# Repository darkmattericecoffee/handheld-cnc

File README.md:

## Description
Compass is a DIY handheld CNC router designed to make CNC machining more accessible.

Unlike traditional CNC machines that move a cutting tool within a fixed workspace, Compass relies on users to guide the device around the workpiece directly. It automatically adjusts the cutting tool to stay on the programmed design path, enabling a significantly smaller device footprint while still handling large-scale cuts.

This is all accomplished using optical flow mouse sensors to track the position of the device, as well as a lead screw driven gantry to adjust the tool. The brains are a Teensy 4.1 microcontroller.

## Getting Started
This repo contains all of the source to build a Handheld CNC Router: the firmware, CAD files for 3D printing/manufacturing, BOM, and cable diagrams.

### Navigation
Internal
- [main](main/) - main firmware (written for [PlatformIO](https://docs.platformio.org/en/latest/core/quickstart.html) usage)
- [cad](cad/) - custom hardware (3D prints, laser cut sheet metal, cable harnesses)
- [pcb](pcb/) - printed circuit board designs for motherboard and sensors
- [dev](dev/) - development folder for debugging and testing

External
- [BOM](https://docs.google.com/spreadsheets/d/12QS1CGSAB-lqKIOotCXDaXmJv9cjfRvVEAgQbRd7MnY/edit?usp=sharing)
- [Assembly Instructions](https://drive.google.com/drive/folders/1fIALrTWUbJRqTl93RGrUaR8dMfO7AI_g?usp=sharing)

## Disclaimer
This project is a work-in-progress. Development is rapidly occurring, so design files and firmware may change.

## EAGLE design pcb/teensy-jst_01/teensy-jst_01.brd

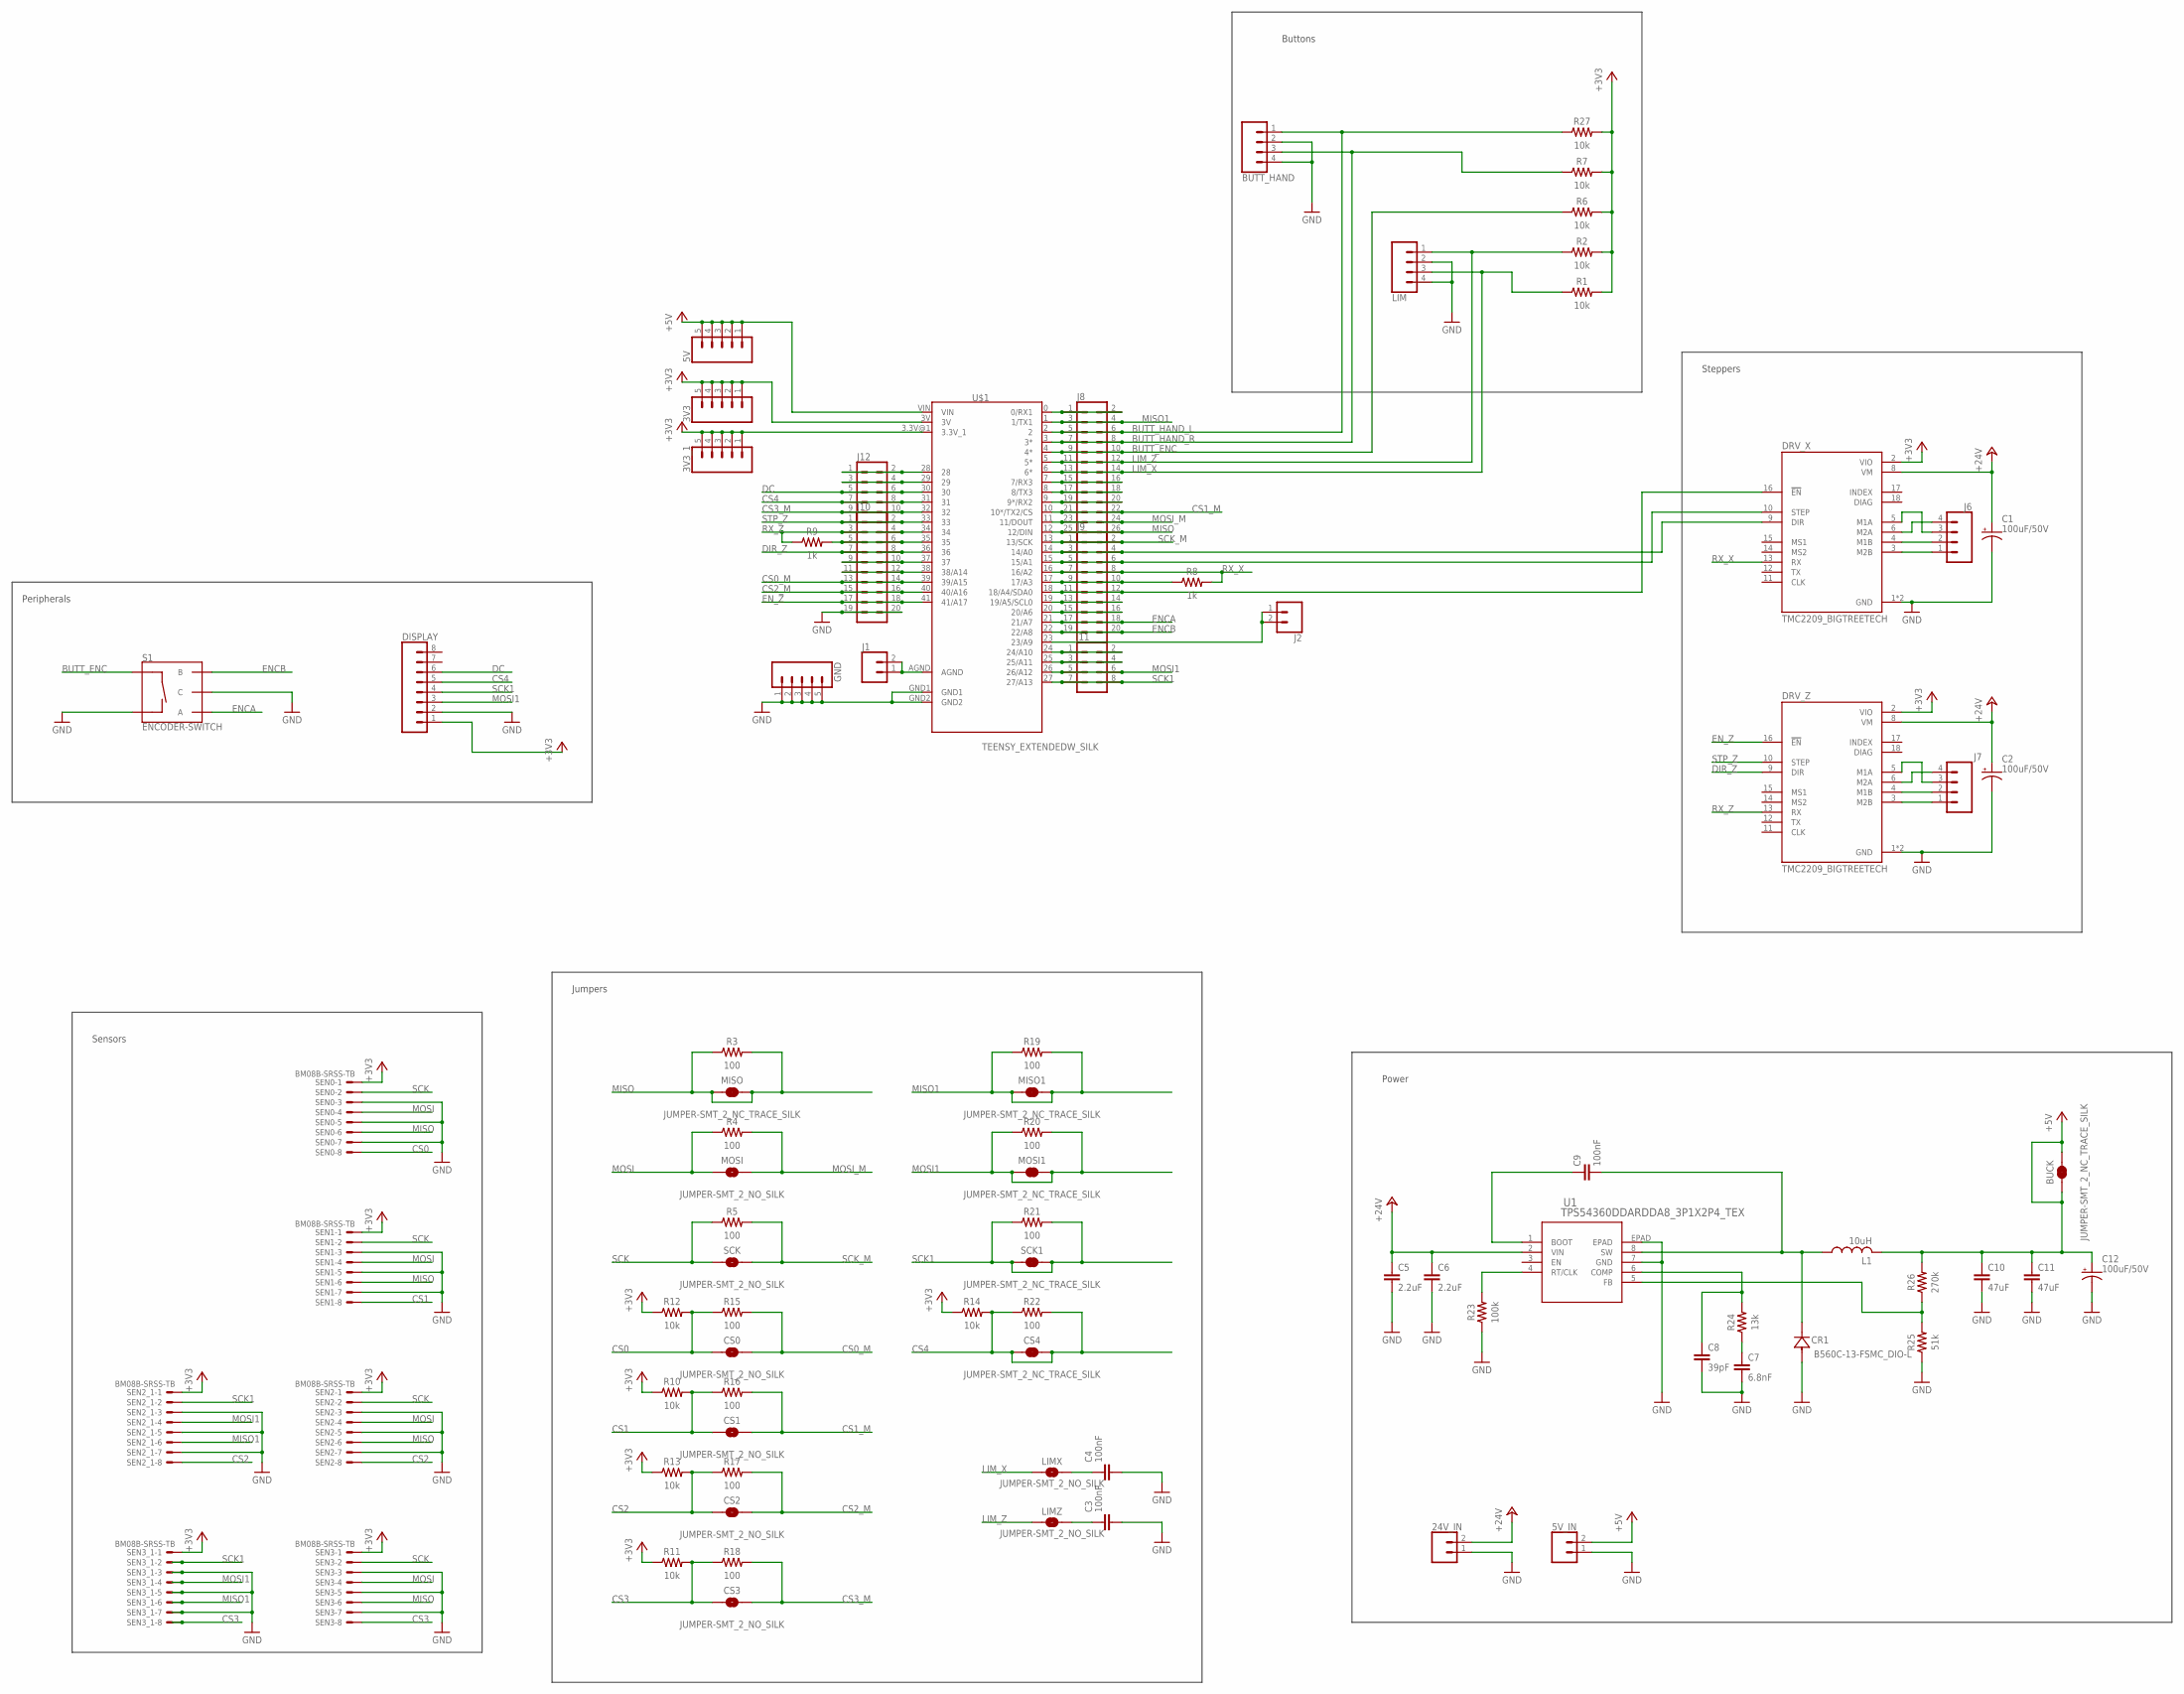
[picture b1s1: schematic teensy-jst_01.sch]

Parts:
3V3, 3V3_1, 5V: CONN_05PTH; 1X05
5V_IN, 24V_IN: CONN_025MM; SCREWTERMINAL-5MM-2
BUCK: JUMPER-SMT_2_NC_TRACE_SILK; SMT-JUMPER_2_NC_TRACE_SILK
BUTT_HAND: CONN_041X04_NO_SILK; 1X04_NO_SILK
C1, C2, C12: 100uF/50V; E5-6
C3, C4: 100nF; C0603
C5, C6: 2.2uF; C0603
C7: 6.8nF; C0402
C8: 39pF; C0402
C9: 100nF; C0402
C10, C11: 47uF; C0603
CR1: B560C-13-FSMC_DIO-L; SMC_DIO-L
CS0, CS1, CS2, CS3: JUMPER-SMT_2_NO_SILK; SMT-JUMPER_2_NO_SILK
CS4: JUMPER-SMT_2_NC_TRACE_SILK; SMT-JUMPER_2_NC_TRACE_SILK
DISPLAY: CONN_08"; 1X08
DRV_X: TMC2209_BIGTREETECH; MODULE_TMC2209_BIGTREETECH
DRV_Z: TMC2209_BIGTREETECH; MODULE_TMC2209_BIGTREETECH
GND: CONN_05PTH; 1X05
J1, J2: CONN_02; 1X02
J6, J7: CONN_04PTH; 1X04
J8: CONN_13X22X13; 2X13
J9, J10: CONN_10X2; 2X10
J11: CONN_04X2; 2X4
J12: CONN_05X2PTH; 2X5
L1: 10uH; MWSA0503S-100MT
LIM: CONN_041X04_NO_SILK; 1X04_NO_SILK
LIMX: JUMPER-SMT_2_NO_SILK; SMT-JUMPER_2_NO_SILK
LIMZ: JUMPER-SMT_2_NO_SILK; SMT-JUMPER_2_NO_SILK
MISO, MISO1: JUMPER-SMT_2_NC_TRACE_SILK; SMT-JUMPER_2_NC_TRACE_SILK
MOSI: JUMPER-SMT_2_NO_SILK; SMT-JUMPER_2_NO_SILK
MOSI1: JUMPER-SMT_2_NC_TRACE_SILK; SMT-JUMPER_2_NC_TRACE_SILK
R1, R2, R6, R7, R10, R11, R12, R13, R14, R27: 10k; RESC1608X60
R3, R4, R5, R15, R16, R17, R18, R19, R20, R21, R22: 100; RESC1608X60
R8, R9: 1k; RESC1608X60
R23: 100k; RESC1005X40
R24: 13k; RESC1005X40
R25: 51k; RESC1005X40
R26: 270k; RESC1005X40
S1: ENCODER-SWITCH; ROTARY_ENC_PLAIN
SCK: JUMPER-SMT_2_NO_SILK; SMT-JUMPER_2_NO_SILK
SCK1: JUMPER-SMT_2_NC_TRACE_SILK; SMT-JUMPER_2_NC_TRACE_SILK
SEN0, SEN1, SEN2, SEN2_1, SEN3, SEN3_1: BM08B-SRSS-TB
U1: TPS54360DDARDDA8_3P1X2P4_TEX; DDA8_3P1X2P4_TEX
U$1: TEENSY_EXTENDEDW_SILK; TEENSY_EXTENDED

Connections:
+3V3: 3V3.1, 3V3.2, 3V3.3, 3V3.4, 3V3.5, 3V3_1.1, 3V3_1.2, 3V3_1.3, 3V3_1.4, 3V3_1.5, DISPLAY.1, DRV_X.2 (VIO), DRV_Z.2 (VIO), R1.2, R2.2, R6.2, R7.2, R10.1, R11.1, R12.1, R13.1, R14.1, R27.2, SEN0.1, SEN1.1, SEN2.1, SEN2_1.1, SEN3.1, SEN3_1.1, U$1.3.3V@1 (3.3V_1), U$1.3V
+5V: 5V.1, 5V.2, 5V.3, 5V.4, 5V.5, 5V_IN.2, BUCK.1, BUCK.2, C10.1, C11.1, C12.+, L1.2, R26.2, U$1.VIN
+24V: 24V_IN.2, C1.+, C2.+, C5.1, C6.1, DRV_X.8 (VM), DRV_Z.8 (VM), U1.2 (VIN)
BUTT_ENC: J8.9, J8.10, R6.1, S1.SW+, U$1.4 (4*)
BUTT_HAND_L: BUTT_HAND.1, J8.5, J8.6, R27.1, U$1.2
BUTT_HAND_R: BUTT_HAND.3, J8.7, J8.8, R7.1, U$1.3 (3*)
CS0: CS0.1, R12.2, R15.1, SEN0.8
CS0_M: CS0.2, J10.13, J10.14, R15.2, U$1.39 (39/A15)
CS1: CS1.1, R10.2, R16.1, SEN1.8
CS1_M: CS1.2, J8.21, J8.22, R16.2, U$1.10 (10*/TX2/CS)
CS2: CS2.1, R13.2, R17.1, SEN2.8, SEN2_1.8
CS2_M: CS2.2, J10.15, J10.16, R17.2, U$1.40 (40/A16)
CS3: CS3.1, R11.2, R18.1, SEN3.8, SEN3_1.8
CS3_M: CS3.2, J12.9, J12.10, R18.2, U$1.32
CS4: CS4.1, CS4.2, DISPLAY.5, J12.7, J12.8, R14.2, R22.1, R22.2, U$1.31
DC: DISPLAY.6, J12.5, J12.6, U$1.30
DIR_Z: DRV_Z.9 (DIR), J10.7, J10.8, U$1.36
ENCA: J9.17, J9.18, S1.A, U$1.21 (21/A7)
ENCB: J9.19, J9.20, S1.B, U$1.22 (22/A8)
EN_Z: DRV_Z.16 (!EN), J10.17, J10.18, U$1.41 (41/A17)
GND: 5V_IN.1, 24V_IN.1, BUTT_HAND.2, BUTT_HAND.4, C1.-, C2.-, C3.2, C4.2, C5.2, C6.2, C7.2, C8.2, C10.2, C11.2, C12.-, CR1.2, DISPLAY.2, DRV_X.1 (GND), DRV_X.7 (GND), DRV_Z.1 (GND), DRV_Z.7 (GND), GND.1, GND.2, GND.3, GND.4, GND.5, J10.19, J10.20, LIM.2, LIM.4, R23.1, R25.1, S1.C, S1.SW-, SEN0.3, SEN0.5, SEN0.7, SEN1.3, SEN1.5, SEN1.7, SEN2.3, SEN2.5, SEN2.7, SEN2_1.3, SEN2_1.5, SEN2_1.7, SEN3.3, SEN3.5, SEN3.7, SEN3_1.3, SEN3_1.5, SEN3_1.7, U1.7 (GND), U1.EPAD, U$1.GND1, U$1.GND2
LIM_X: J8.13, J8.14, LIM.3, LIMX.1, R1.1, U$1.6 (6*)
LIM_Z: J8.11, J8.12, LIM.1, LIMZ.1, R2.1, U$1.5 (5*)
MISO: J8.25, J8.26, MISO.1, MISO.2, R3.1, R3.2, SEN0.6, SEN1.6, SEN2.6, SEN3.6, U$1.12 (12/DIN)
MISO1: J8.3, J8.4, MISO1.1, MISO1.2, R19.1, R19.2, SEN2_1.6, SEN3_1.6, U$1.1 (1/TX1)
MOSI: MOSI.1, R4.1, SEN0.4, SEN1.4, SEN2.4, SEN3.4
MOSI1: DISPLAY.3, J11.5, J11.6, MOSI1.1, MOSI1.2, R20.1, R20.2, SEN2_1.4, SEN3_1.4, U$1.26 (26/A12)
MOSI_M: J8.23, J8.24, MOSI.2, R4.2, U$1.11 (11/DOUT)
MS1_Z: J10.9, J10.10, U$1.37
MS2_Z: J10.11, J10.12, U$1.38 (38/A14)
unnamed: J12.1, J12.2, U$1.28
unnamed: J11.1, J11.2, U$1.24 (24/A10)
unnamed: J1.1, J1.2, U$1.AGND
unnamed: J2.1, J2.2, U$1.23 (23/A9)
unnamed: J12.3, J12.4, U$1.29
unnamed: R23.2, U1.4 (RT/CLK)
unnamed: J8.15, J8.16, U$1.7 (7/RX3)
unnamed: C7.1, R24.1
unnamed: DRV_X.9 (DIR), J9.3, J9.4, U$1.14 (14/A0)
unnamed: DRV_Z.6 (M2A), J7.4
unnamed: DRV_X.10 (STEP), J9.5, J9.6, U$1.15 (15/A1)
unnamed: C8.1, R24.2, U1.6 (COMP)
unnamed: DRV_Z.5 (M1A), J7.3
unnamed: J9.13, J9.14, U$1.19 (19/A5/SCL0)
unnamed: DRV_X.6 (M2A), J6.4
unnamed: DRV_X.5 (M1A), J6.3
unnamed: R25.2, R26.1, U1.5 (FB)
unnamed: DRV_Z.4 (M1B), J7.2
unnamed: DRV_Z.3 (M2B), J7.1
unnamed: J11.3, J11.4, U$1.25 (25/A11)
unnamed: C3.1, LIMZ.2
unnamed: DRV_X.4 (M1B), J6.2
unnamed: DRV_X.3 (M2B), J6.1
unnamed: J9.15, J9.16, U$1.20 (20/A6)
unnamed: DRV_X.16 (!EN), J9.11, J9.12, U$1.18 (18/A4/SDA0)
unnamed: J9.9, J9.10, R8.1, U$1.17 (17/A3)
unnamed: C9.2, CR1.1, L1.1, U1.8 (SW)
unnamed: C4.1, LIMX.2
unnamed: C9.1, U1.1 (BOOT)
unnamed: J8.17, J8.18, U$1.8 (8/TX3)
unnamed: J8.1, J8.2, U$1.0 (0/RX1)
unnamed: J8.19, J8.20, U$1.9 (9*/RX2)
unnamed: J10.5, J10.6, R9.2, U$1.35
RX_X: DRV_X.13 (RX), J9.7, J9.8, R8.2, U$1.16 (16/A2)
RX_Z: DRV_Z.13 (RX), J10.3, J10.4, R9.1, U$1.34
SCK: R5.1, SCK.1, SEN0.2, SEN1.2, SEN2.2, SEN3.2
SCK1: DISPLAY.4, J11.7, J11.8, R21.1, R21.2, SCK1.1, SCK1.2, SEN2_1.2, SEN3_1.2, U$1.27 (27/A13)
SCK_M: J9.1, J9.2, R5.2, SCK.2, U$1.13 (13/SCK)
STP_Z: DRV_Z.10 (STEP), J10.1, J10.2, U$1.33

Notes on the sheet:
Jumpers
Peripherals
Steppers
Sensors
Power
Buttons

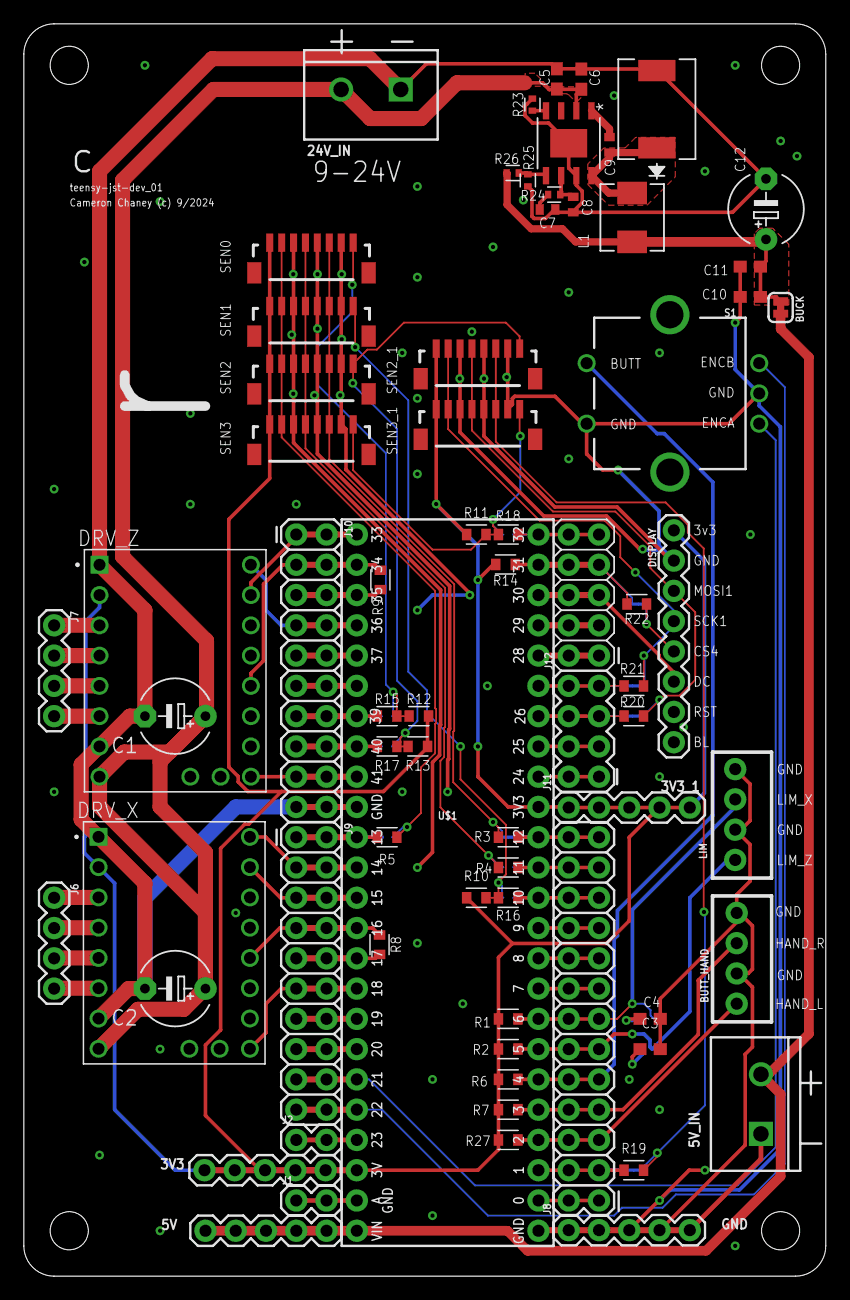
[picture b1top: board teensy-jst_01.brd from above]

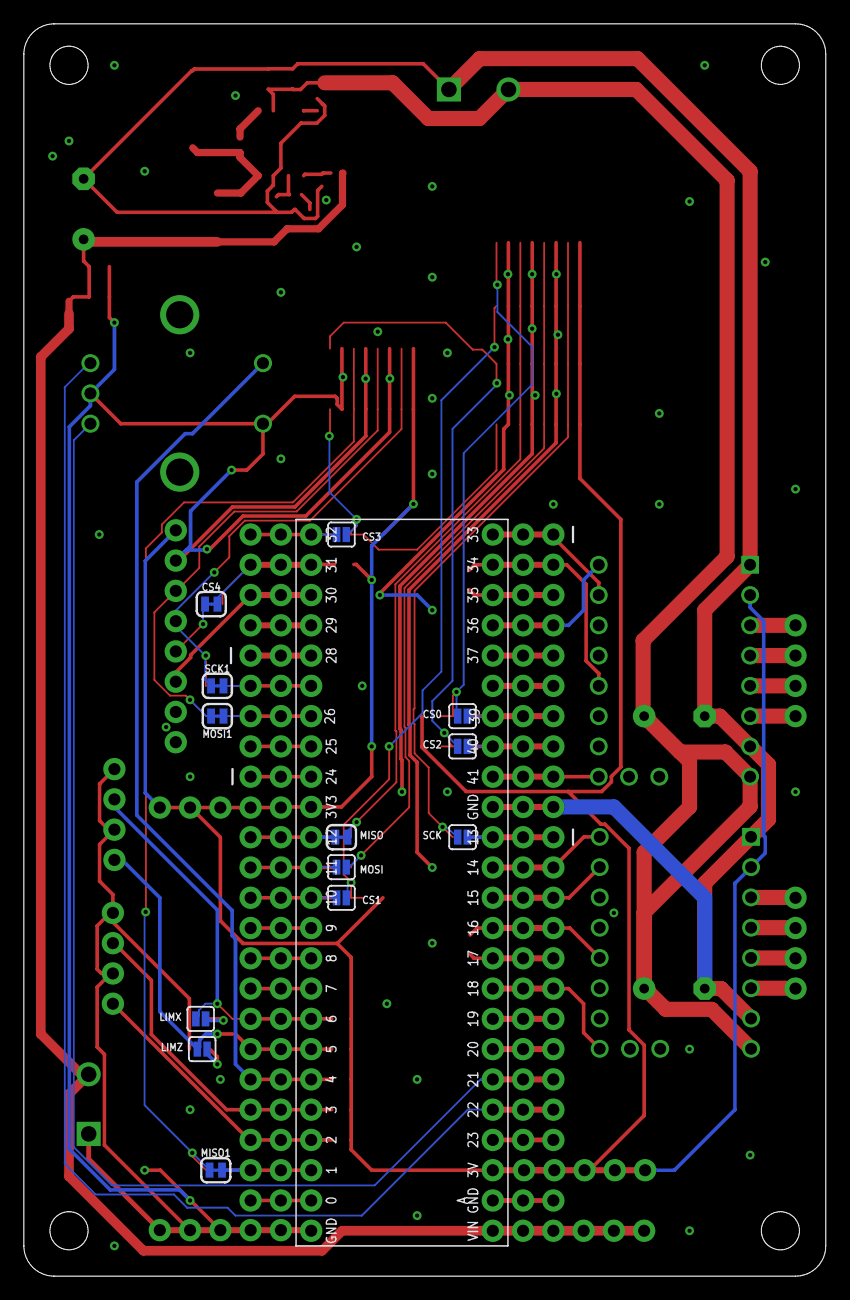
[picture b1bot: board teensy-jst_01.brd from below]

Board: 2 copper layers, 67.3 x 105.1 mm, 84 parts (13 on the bottom side), 69 nets.

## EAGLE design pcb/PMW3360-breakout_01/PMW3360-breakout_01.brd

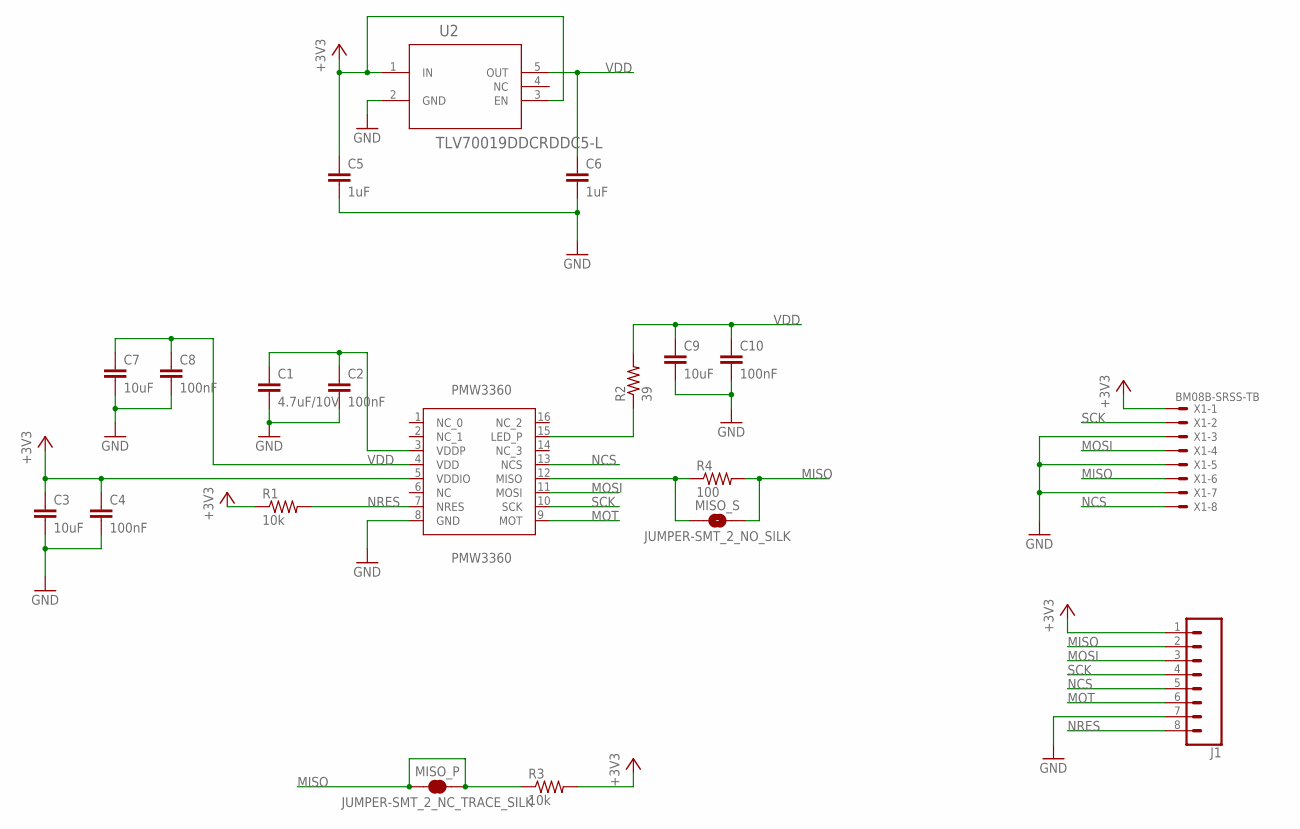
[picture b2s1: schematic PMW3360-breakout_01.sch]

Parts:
C1: 4.7uF/10V; C0603
C2, C4, C8, C10: 100nF; C0402
C3, C7, C9: 10uF; C0402
C5, C6: 1uF; C0402
J1: CONN_08"; 1X08
MISO_P: JUMPER-SMT_2_NC_TRACE_SILK; SMT-JUMPER_2_NC_TRACE_SILK
MISO_S: JUMPER-SMT_2_NO_SILK; SMT-JUMPER_2_NO_SILK
PMW3360: PMW3360
R1, R3: 10k; R0402
R2: 39; R0402
R4: 100; R0402
U2: TLV70019DDCRDDC5-L; DDC5-L
X1: BM08B-SRSS-TB

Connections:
+3V3: C3.1, C4.1, C5.1, J1.1, PMW3360.5 (VDDIO), R1.1, R3.2, U2.1 (IN), U2.3 (EN), X1.1
GND: C1.2, C2.2, C3.2, C4.2, C5.2, C6.2, C7.2, C8.2, C9.2, C10.2, J1.7, PMW3360.8 (GND), U2.2 (GND), X1.3, X1.5, X1.7
MISO: J1.2, MISO_P.1, MISO_P.2, MISO_S.2, R3.1, R4.2, X1.6
MOSI: J1.3, PMW3360.11 (MOSI), X1.4
MOT: J1.6, PMW3360.9 (MOT)
unnamed: PMW3360.15 (LED_P), R2.1
unnamed: C1.1, C2.1, PMW3360.3 (VDDP)
unnamed: MISO_S.1, PMW3360.12 (MISO), R4.1
NCS: J1.5, PMW3360.13 (NCS), X1.8
NRES: J1.8, PMW3360.7 (NRES), R1.2
SCK: J1.4, PMW3360.10 (SCK), X1.2
VDD: C6.1, C7.1, C8.1, C9.1, C10.1, PMW3360.4 (VDD), R2.2, U2.5 (OUT)

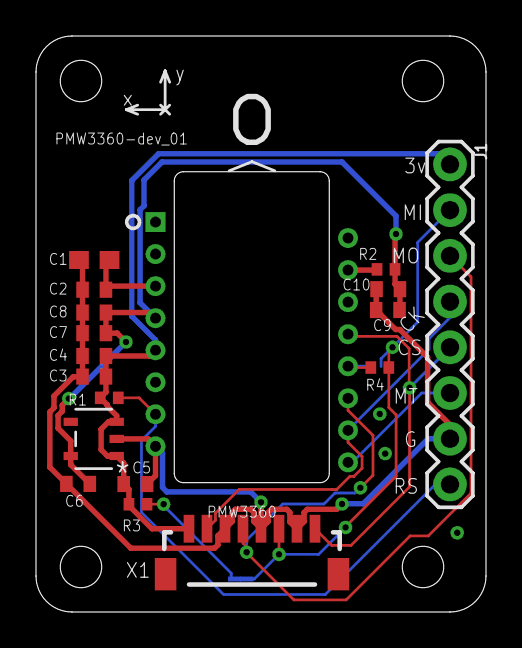
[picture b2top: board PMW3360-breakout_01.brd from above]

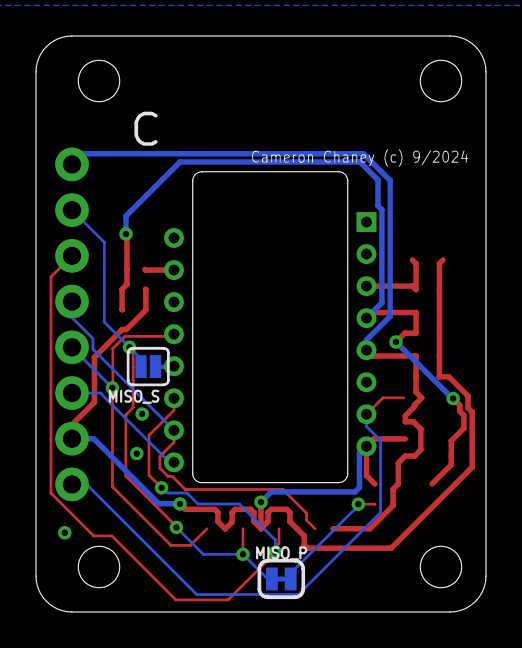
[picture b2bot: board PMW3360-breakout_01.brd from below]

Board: 2 copper layers, 25.0 x 32.0 mm, 20 parts (2 on the bottom side), 12 nets.

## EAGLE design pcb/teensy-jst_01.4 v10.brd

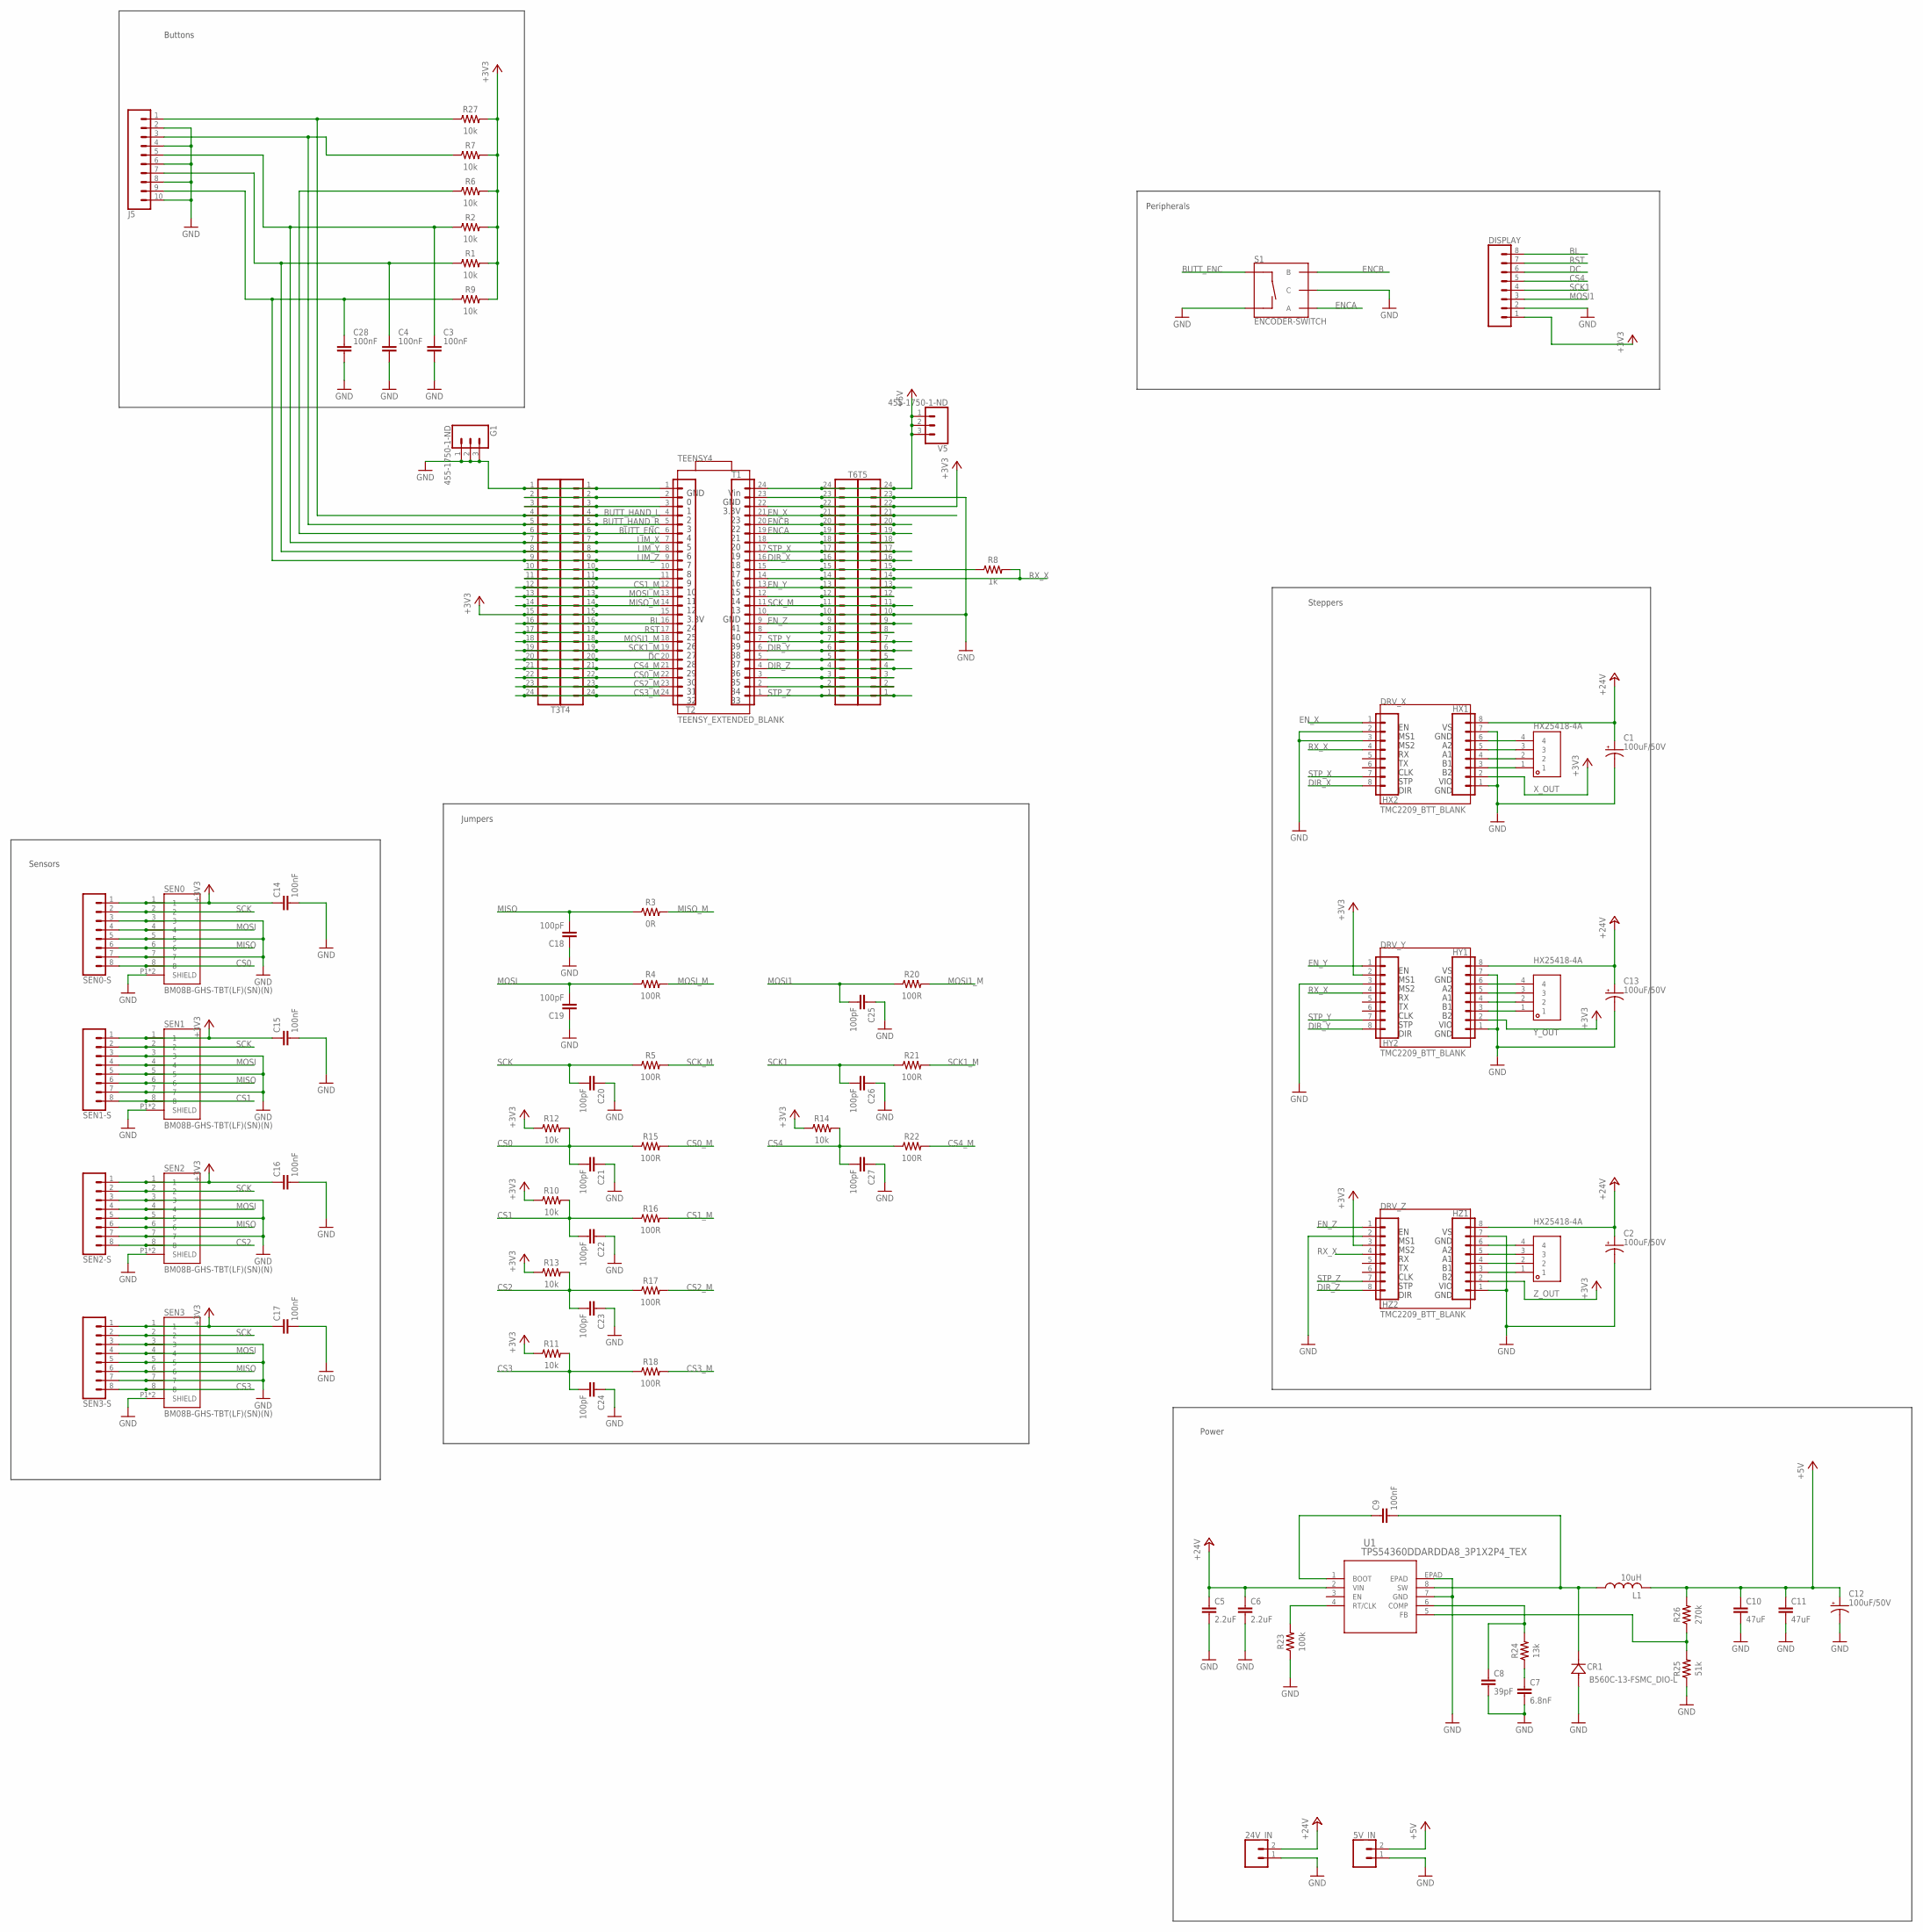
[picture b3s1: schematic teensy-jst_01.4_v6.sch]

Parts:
5V_IN, 24V_IN: CONN_025MM; SCREWTERMINAL-5MM-2
C1, C2, C12, C13: 100uF/50V; PANASONIC_D
C3, C4, C28: 100nF; CAPC1608X85
C5, C6: 2.2uF; CAPC1608X85
C7: 6.8nF; CAPC1608X85
C8: 39pF; CAPC1005X60
C9, C14, C15, C16, C17: 100nF; CAPC1005X60
C10, C11: 47uF; CAPC2012X110
C18, C19, C20, C21, C22, C23, C24, C25, C26, C27: 100pF; CAPC1005X60
CR1: B560C-13-FSMC_DIO-L; SMC_DIO-L
DISPLAY: CONN_08"; 1X08
DRV_X: TMC2209_BTT_BLANK; MODULE_TMC2209_BTT_BLANK
DRV_Y: TMC2209_BTT_BLANK; MODULE_TMC2209_BTT_BLANK
DRV_Z: TMC2209_BTT_BLANK; MODULE_TMC2209_BTT_BLANK
G1: 455-1750-1-ND; 1X03
HX1, HX2: CONN_08"; 1X08
HY1, HY2: CONN_08"; 1X08
HZ1, HZ2: CONN_08"; 1X08
J5: CONN_10"; 1X10
L1: 10uH; MWSA0503S-100MT
R1, R2, R6, R7, R9, R10, R11, R12, R13, R14, R27: 10k; RESC1608X60
R3: 0R; RESC1608X60
R4, R5, R15, R16, R17, R18, R20, R21, R22: 100R; RESC1608X60
R8: 1k; RESC1608X60
R23: 100k; RESC1005X40
R24: 13k; RESC1608X60
R25: 51k; RESC1608X60
R26: 270k; RESC1005X40
S1: ENCODER-SWITCH; ROTARY_ENC_PLAIN
SEN0, SEN1, SEN2, SEN3: BM08B-GHS-TBT(LF)(SN)(N); JST_BM08B-GHS-TBT(LF)(SN)(N)
SEN0-S, SEN1-S, SEN2-S, SEN3-S: CONN_08"; 1X08
T1, T2, T3, T4, T5, T6: CONN_24; 1X24
TEENSY4: TEENSY_EXTENDED_BLANK
U1: TPS54360DDARDDA8_3P1X2P4_TEX; DDA8_3P1X2P4_TEX
V5: 455-1750-1-ND; 1X03
X_OUT: HX25418-4A
Y_OUT: HX25418-4A
Z_OUT: HX25418-4A

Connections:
+3V3: C14.1, C15.1, C16.1, C17.1, DISPLAY.1, HX1.2, HY1.2, HY2.2, HZ1.2, HZ2.3, R1.2, R2.2, R6.2, R7.2, R9.2, R10.1, R11.1, R12.1, R13.1, R14.1, R27.2, SEN0.1, SEN0-S.1, SEN1.1, SEN1-S.1, SEN2.1, SEN2-S.1, SEN3.1, SEN3-S.1, T1.22, T2.15, T3.15, T4.15, T5.22, T6.22
+5V: 5V_IN.2, C10.1, C11.1, C12.+, L1.2, R26.2, T1.24, T5.24, T6.24, V5.1, V5.2, V5.3
+24V: 24V_IN.2, C1.+, C2.+, C5.1, C6.1, C13.+, HX1.8, HY1.8, HZ1.8, U1.2 (VIN)
BL: DISPLAY.8, T2.16, T3.16, T4.16
BUTT_ENC: R6.1, S1.SW+, T2.6, T3.6, T4.6
BUTT_HAND_L: J5.1, R27.1, T2.4, T3.4, T4.4
BUTT_HAND_R: J5.3, R7.1, T2.5, T3.5, T4.5
CS0: C21.2, R12.2, R15.1, SEN0.8, SEN0-S.8
CS0_M: R15.2, T2.22, T3.22, T4.22
CS1: C22.2, R10.2, R16.1, SEN1.8, SEN1-S.8
CS1_M: R16.2, T2.12, T3.12, T4.12
CS2: C23.2, R13.2, R17.1, SEN2.8, SEN2-S.8
CS2_M: R17.2, T2.23, T3.23, T4.23
CS3: C24.2, R11.2, R18.1, SEN3.8, SEN3-S.8
CS3_M: R18.2, T2.24, T3.24, T4.24
CS4: C27.2, DISPLAY.5, R14.2, R22.1
CS4_M: R22.2, T2.21, T3.21, T4.21
DC: DISPLAY.6, T2.20, T3.20, T4.20
DIR_X: HX2.8, T1.16, T5.16, T6.16
DIR_Y: HY2.8, T1.6, T5.6, T6.6
DIR_Z: HZ2.8, T1.4, T5.4, T6.4
ENCA: S1.A, T1.19, T5.19, T6.19
ENCB: S1.B, T1.20, T5.20, T6.20
EN_X: HX2.1, T1.21, T5.21, T6.21
EN_Y: HY2.1, T1.13, T5.13, T6.13
EN_Z: HZ2.1, T1.9, T5.9, T6.9
GND: 5V_IN.1, 24V_IN.1, C1.-, C2.-, C3.2, C4.2, C5.2, C6.2, C7.2, C8.2, C10.2, C11.2, C12.-, C13.-, C14.2, C15.2, C16.2, C17.2, C18.1, C19.1, C20.1, C21.1, C22.1, C23.1, C24.1, C25.1, C26.1, C27.1, C28.2, CR1.2, DISPLAY.2, G1.1, G1.2, G1.3, HX1.1, HX1.7, HX2.2, HX2.3, HY1.1, HY1.7, HY2.3, HZ1.1, HZ1.7, HZ2.2, J5.2, J5.4, J5.6, J5.8, J5.10, R23.1, R25.1, S1.C, S1.SW-, SEN0.3, SEN0.5, SEN0.7, SEN0.P1 (SHIELD), SEN0.P2 (SHIELD), SEN0-S.3, SEN0-S.5, SEN0-S.7, SEN1.3, SEN1.5, SEN1.7, SEN1.P1 (SHIELD), SEN1.P2 (SHIELD), SEN1-S.3, SEN1-S.5, SEN1-S.7, SEN2.3, SEN2.5, SEN2.7, SEN2.P1 (SHIELD), SEN2.P2 (SHIELD), SEN2-S.3, SEN2-S.5, SEN2-S.7, SEN3.3, SEN3.5, SEN3.7, SEN3.P1 (SHIELD), SEN3.P2 (SHIELD), SEN3-S.3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
LIM_X: C3.1, J5.5, R2.1, T2.7, T3.7, T4.7
LIM_Y: C4.1, J5.7, R1.1, T2.8, T3.8, T4.8
LIM_Z: C28.1, J5.9, R9.1, T2.9, T3.9, T4.9
MISO: C18.2, R3.1, SEN0.6, SEN0-S.6, SEN1.6, SEN1-S.6, SEN2.6, SEN2-S.6, SEN3.6, SEN3-S.6
MISO_M: R3.2, T2.14, T3.14, T4.14
MOSI: C19.2, R4.1, SEN0.4, SEN0-S.4, SEN1.4, SEN1-S.4, SEN2.4, SEN2-S.4, SEN3.4, SEN3-S.4
MOSI1: C25.2, DISPLAY.3, R20.1
MOSI1_M: R20.2, T2.18, T3.18, T4.18
MOSI_M: R4.2, T2.13, T3.13, T4.13
unnamed: T2.2, T3.2, T4.2
unnamed: T2.3, T3.3, T4.3
unnamed: T2.10, T3.10, T4.10
unnamed: T2.11, T3.11, T4.11
unnamed: R23.2, U1.4 (RT/CLK)
unnamed: T1.12, T5.12, T6.12
unnamed: C7.1, R24.1
unnamed: T1.3, T5.3, T6.3
unnamed: HZ1.6, Z_OUT.4
unnamed: T1.2, T5.2, T6.2
unnamed: C8.1, R24.2, U1.6 (COMP)
unnamed: HZ1.5, Z_OUT.3
unnamed: T1.8, T5.8, T6.8
unnamed: HX1.6, X_OUT.4
unnamed: HX1.5, X_OUT.3
unnamed: R25.2, R26.1, U1.5 (FB)
unnamed: HZ1.4, Z_OUT.2
unnamed: HZ1.3, Z_OUT.1
unnamed: T1.18, T5.18, T6.18
unnamed: HY1.4, Y_OUT.2
unnamed: HX1.4, X_OUT.2
unnamed: HX1.3, X_OUT.1
unnamed: T1.5, T5.5, T6.5
unnamed: R8.1, T1.15, T5.15, T6.15
unnamed: HY1.3, Y_OUT.1
unnamed: C9.2, CR1.1, L1.1, U1.8 (SW)
unnamed: C9.1, U1.1 (BOOT)
unnamed: HY1.6, Y_OUT.4
unnamed: HY1.5, Y_OUT.3
RST: DISPLAY.7, T2.17, T3.17, T4.17
RX_X: HX2.4, HY2.4, HZ2.4, R8.2, T1.14, T5.14, T6.14
SCK: C20.2, R5.1, SEN0.2, SEN0-S.2, SEN1.2, SEN1-S.2, SEN2.2, SEN2-S.2, SEN3.2, SEN3-S.2
SCK1: C26.2, DISPLAY.4, R21.1
SCK1_M: R21.2, T2.19, T3.19, T4.19
SCK_M: R5.2, T1.11, T5.11, T6.11
STP_X: HX2.7, T1.17, T5.17, T6.17
STP_Y: HY2.7, T1.7, T5.7, T6.7
STP_Z: HZ2.7, T1.1, T5.1, T6.1

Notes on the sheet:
Jumpers
Peripherals
Steppers
Sensors
Power
Buttons

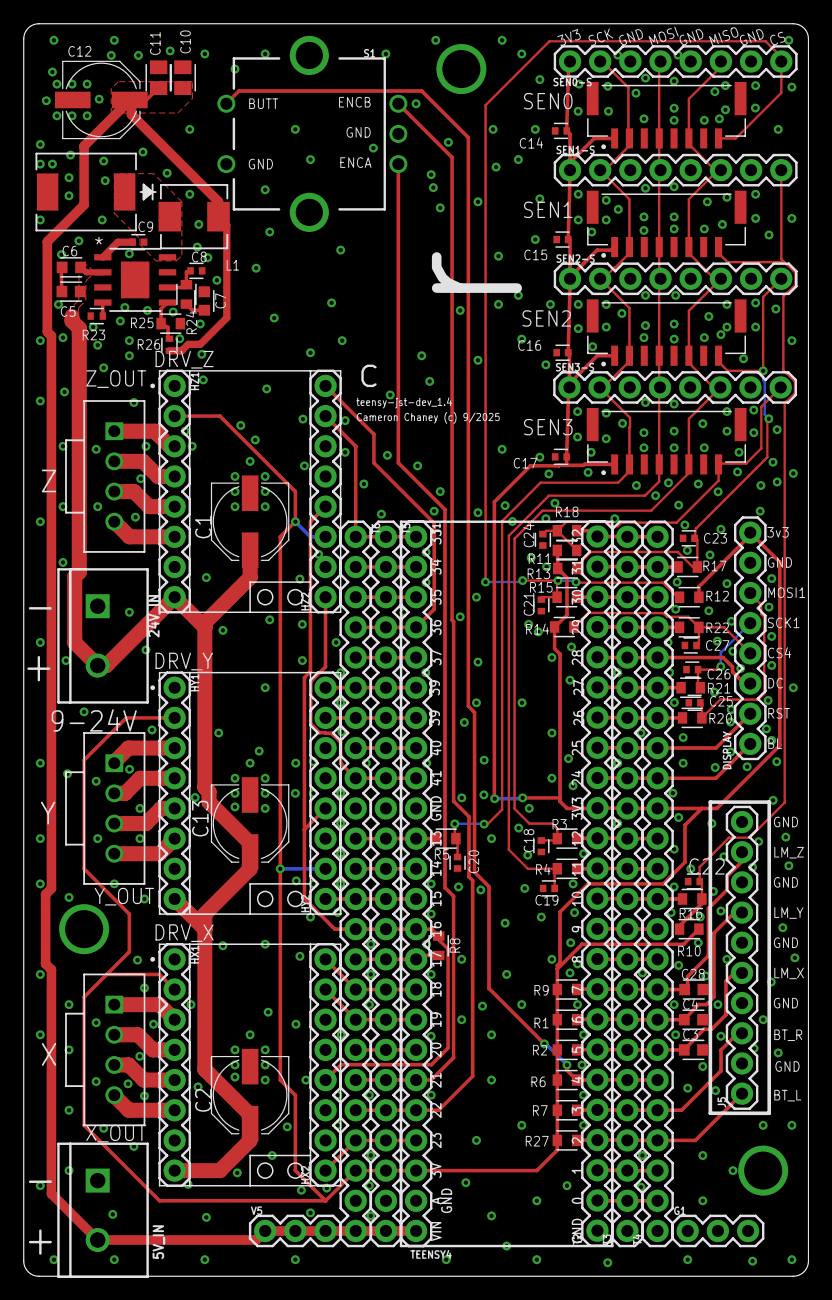
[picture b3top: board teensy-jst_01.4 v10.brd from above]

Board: 2 copper layers, 66.0 x 105.4 mm, 91 parts (0 on the bottom side), 74 nets.

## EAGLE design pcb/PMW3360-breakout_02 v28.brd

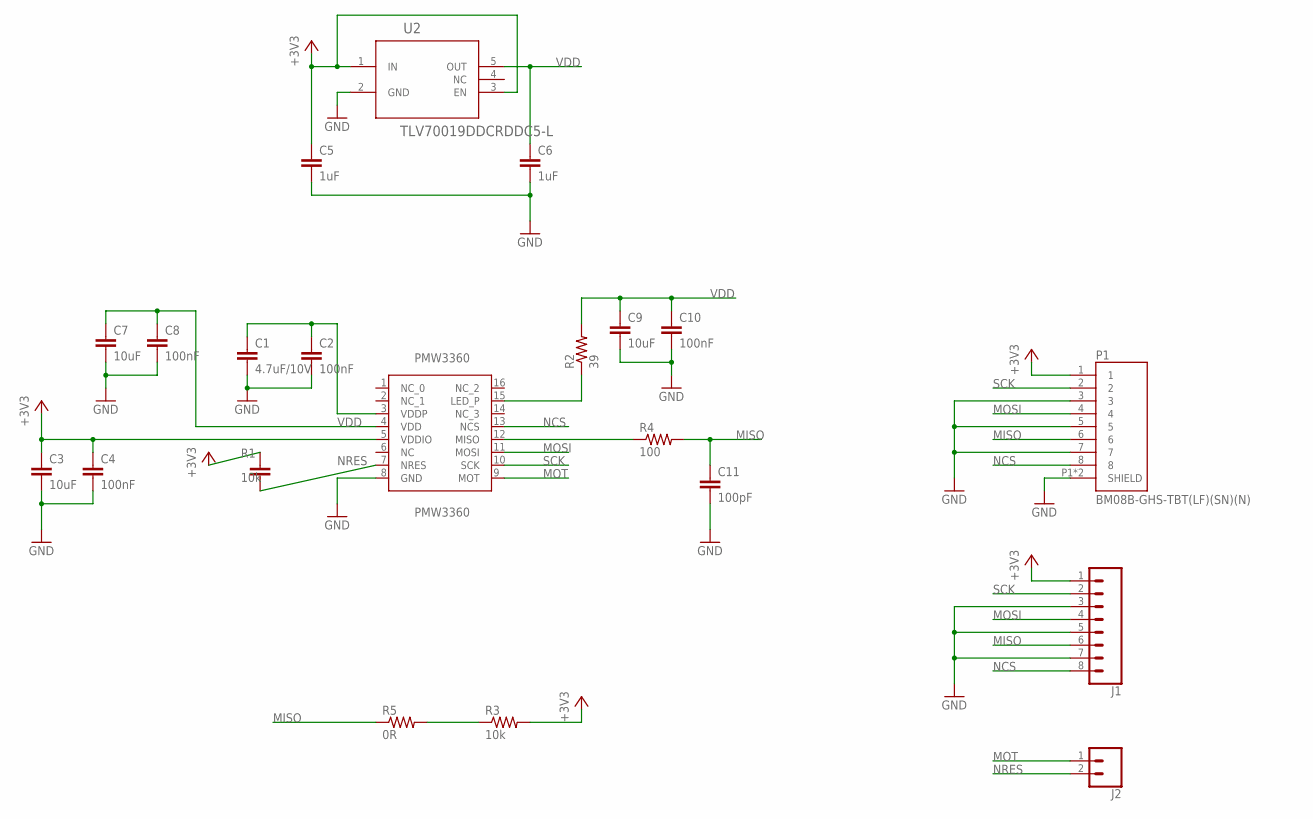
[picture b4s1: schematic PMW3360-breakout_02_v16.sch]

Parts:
C1: 4.7uF/10V; CAPC1608X85
C2, C4, C8, C10: 100nF; CAPC1005X60
C3, C7, C9: 10uF; CAPC1005X60
C5, C6: 1uF; CAPC1005X60
C11: 100pF; CAPC1005X60
J1: CONN_08"; 1X08
J2: CONN_02; 1X02
P1: BM08B-GHS-TBT(LF)(SN)(N); JST_BM08B-GHS-TBT(LF)(SN)(N)
PMW3360: PMW3360
R1: 10k; CAPC1005X60
R2: 39; R0402
R3: 10k; R0402
R4: 100; R0402
R5: 0R; R0402
U2: TLV70019DDCRDDC5-L; DDC5-L

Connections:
+3V3: C3.1, C4.1, C5.1, J1.1, P1.1, PMW3360.5 (VDDIO), R1.1, R3.2, U2.1 (IN), U2.3 (EN)
GND: C1.2, C2.2, C3.2, C4.2, C5.2, C6.2, C7.2, C8.2, C9.2, C10.2, C11.2, J1.3, J1.5, J1.7, P1.3, P1.5, P1.7, P1.P1 (SHIELD), P1.P2 (SHIELD), PMW3360.8 (GND), U2.2 (GND)
MISO: C11.1, J1.6, P1.6, R4.2, R5.1
MOSI: J1.4, P1.4, PMW3360.11 (MOSI)
MOT: J2.1, PMW3360.9 (MOT)
unnamed: PMW3360.15 (LED_P), R2.1
unnamed: C1.1, C2.1, PMW3360.3 (VDDP)
unnamed: PMW3360.12 (MISO), R4.1
unnamed: R3.1, R5.2
NCS: J1.8, P1.8, PMW3360.13 (NCS)
NRES: J2.2, PMW3360.7 (NRES), R1.2
SCK: J1.2, P1.2, PMW3360.10 (SCK)
VDD: C6.1, C7.1, C8.1, C9.1, C10.1, PMW3360.4 (VDD), R2.2, U2.5 (OUT)

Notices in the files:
parts and their libraries:
SparkFun-Connectors: Licensing: Creative Commons ShareAlike 4.0 International - https://creativecommons.org/licenses/by-sa/4.0
COPYRIGHT: Copyright (C) 2024 Ultra Librarian. All rights reserved.
